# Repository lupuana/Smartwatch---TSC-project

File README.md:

# Smartwatch — TSC Project

> A custom-designed smartwatch based on the **Nordic nRF52840** SoC, featuring an e-paper display interface, haptic feedback, accelerometer-based motion sensing, LiPo battery management, and Bluetooth Low Energy connectivity. The PCB measures **46 × 35 mm** with rounded corners and is designed to fit inside a 3D-printed enclosure.

---

## Table of Contents

1. [Block Diagram](#block-diagram)
2. [Bill of Materials (BOM)](#bill-of-materials-bom)
3. [Hardware Description](#hardware-description)
4. [nRF52840 Pin Assignments](#nrf52840-pin-assignments)
5. [PCB Images](#pcb-images)
6. [Mechanical / Enclosure](#mechanical--enclosure)
7. [Design Notes](#design-notes)

---

## Block Diagram

```
                          ┌───────────────────────────────────────────────────────────────────┐
                          │                        nRF52840 (U1)                              │
                          │   ARM Cortex-M4F @ 64 MHz · 1 MB Flash · 256 KB RAM · BLE 5.0   │
                          └──┬──────────┬──────────┬──────────┬──────────┬──────────┬────────┘
                             │          │          │          │          │          │
                    SPI Bus  │   I2C Bus│  I2C Bus │  GPIO    │  SWD     │  GPIO    │  GPIO
                             │          │          │          │          │          │
               ┌─────────────▼──┐  ┌───▼────┐ ┌──▼──────┐  │   ┌──────▼──────┐  ┌▼───────┐
               │  E-Paper (EPD) │  │ BMA423 │ │DRV2605  │  │   │ TC2030-IDC  │  │ 3× SW  │
               │  24-pin FPC    │  │ Accel. │ │ Haptic  │  │   │ SWD Debug   │  │(UP/DN/ │
               │  (J1 Molex)    │  │ (IC3)  │ │ Driver  │  │   │ Connector   │  │  ENT)  │
               └────────────────┘  └────────┘ │ (IC2)   │  │   └─────────────┘  └────────┘
                                              └─────────┘  │
                                                           │
                          ┌────────────────────────────────┼──────────────────────────────────┐
                          │              Power System       │                                  │
                          │                                 │                                  │
               ┌──────────▼──┐   ┌──────────┐   ┌────────▼──────┐   ┌──────────────────┐   │
               │ USB Type-C  │   │BQ25180   │   │  MAX17048     │   │   RT6160AWSC     │   │
               │  (J4)       ├──►│ LiPo     │   │  Fuel Gauge   │   │  Buck-Boost Reg. │   │
               │ + ESD D3    │   │ Charger  │   │  (U3) I2C     │   │  (IC9) I2C       │   │
               └─────────────┘   │ (IC1)    │   └───────────────┘   └──────────────────┘   │
                                 └────┬─────┘                                                │
                                      │ VBAT                                                 │
                                 ┌────▼─────┐                                                │
                                 │  LiPo    │                                                │
                                 │ Battery  │                                                │
                                 │ (J3 pad) │                                                │
                                 └──────────┘                                                │
                                                                                             │
               ┌──────────────────────────────────────────────────────────────────┐          │
               │                    RF Front-End                                   │          │
               │  32 MHz XTAL (X1) · 32.768 kHz XTAL (X2) · ANT1 2.45 GHz       │◄─────────┘
               │  Matching network: L1 3.9 nH · L2 10 µH · L3 15 nH             │
               └──────────────────────────────────────────────────────────────────┘
```

---

## Bill of Materials (BOM)

> Procurement links point to **JLCPCB Parts** where available; datasheets linked to official manufacturer sources.

| Ref(s) | Qty | Value / Part | Description | Package | JLCPCB / Buy Link | Datasheet |
|---|---|---|---|---|---|---|
| U1 | 1 | NRF52840-QIAA | Nordic nRF52840 SoC — main MCU, BLE 5.0, ARM Cortex-M4F | AQFN-73 (aQFN50) | [JLCPCB C190794](https://jlcpcb.com/partdetail/NordicSemiconductor-NRF52840_QIAA/C190794) | [Datasheet](https://infocenter.nordicsemi.com/pdf/nRF52840_PS_v1.7.pdf) |
| IC1 | 1 | BQ25180YBGR | 1-cell LiPo charger, I²C programmable, 1 A | 8-DSBGA (1.6×1.1 mm) | [JLCPCB C2828062](https://jlcpcb.com/partdetail/TexasInstruments-BQ25180YBGR/C2828062) | [Datasheet](https://www.ti.com/lit/ds/symlink/bq25180.pdf) |
| IC2 | 1 | DRV2605YZFR | Haptic driver for ERM/LRA motors, I²C, built-in waveform library | 9-BGA (1.44×1.44 mm) | [JLCPCB C529659](https://jlcpcb.com/partdetail/TexasInstruments-DRV2605YZFR/C529659) | [Datasheet](https://www.ti.com/lit/ds/symlink/drv2605.pdf) |
| IC3 | 1 | BMA423 | Triaxial 12-bit accelerometer, step counter, I²C/SPI | LGA-12 (2×2 mm) | [JLCPCB C332973](https://jlcpcb.com/partdetail/BoschSensortec-BMA423/C332973) | [Datasheet](https://www.bosch-sensortec.com/media/boschsensortec/downloads/datasheets/bst-bma423-ds000.pdf) |
| IC9 | 1 | RT6160AWSC | Buck-boost DC-DC converter, I²C, 15-pin WL-CSP | BGA-15 (1.4×2.3 mm) | [JLCPCB C2834980](https://jlcpcb.com/partdetail/Richtek-RT6160AWSC/C2834980) | [Datasheet](https://www.richtek.com/assets/product_file/RT6160A/DS6160A-00.pdf) |
| U3 | 1 | MAX17048G+T10 | 1-cell/2-cell LiPo fuel gauge, I²C ModelGauge | TDFN-8 (2×2 mm) | [JLCPCB C368489](https://jlcpcb.com/partdetail/MaximIntegrated-MAX17048G_T10/C368489) | [Datasheet](https://www.analog.com/media/en/technical-documentation/data-sheets/MAX17048-MAX17049.pdf) |
| J1 | 1 | 503480-2400 | Molex 0.5 mm FPC/FFC 24-circuit RA SMT dual-contact connector (EPD) | — | [Mouser 538-503480-2400](https://www.mouser.com/ProductDetail/Molex/503480-2400) | [Datasheet](https://www.molex.com/en-us/products/part-detail/5034802400) |
| J2 | 1 | TC2030-IDC | Tag-Connect 6-pin SWD programming/debug header (no-drill) | TC2030IDC | [Tag-Connect](https://www.tag-connect.com/product/tc2030-idc-nl) | [Info](https://www.tag-connect.com/wp-content/uploads/bsk-pdf-manager/TC2030-IDC-NL_Datasheet_8.pdf) |
| J4 | 1 | KH-TYPE-C-16P | USB Type-C 16-pin SMT receptacle | — | [LCSC C2832](https://www.lcsc.com/product-detail/USB-Connectors_Kinghelm-KH-TYPE-C-16P_C2832.html) | [Datasheet](https://www.kinghelm.com.cn/product/kh-type-c-16p.html) |
| ANT1 | 1 | 2450AT18B100E | 2.45 GHz chip antenna for BLE | 3216 (1.4 mm H) | [JLCPCB C341461](https://jlcpcb.com/partdetail/JohansonTechnology-2450AT18B100E/C341461) | [Datasheet](https://www.johansontechnology.com/datasheets/2450AT18B100E/2450AT18B100E.pdf) |
| D3 | 1 | USBLC6-2SC6Y | USB ESD protection TVS diode array | SOT-23-6 | [JLCPCB C2687116](https://jlcpcb.com/partdetail/STMicroelectronics-USBLC6_2SC6Y/C2687116) | [Datasheet](https://www.st.com/resource/en/datasheet/usblc6-2.pdf) |
| D2, D4, D5 | 3 | MBR0530 | Schottky diode, 30 V / 500 mA | SOD-123 | [JLCPCB C424037](https://jlcpcb.com/partdetail/OnSemiconductor-MBR0530/C424037) | [Datasheet](https://www.onsemi.com/pdf/datasheet/mbr0530-d.pdf) |
| Q3 | 1 | SI1308EDL-T1-GE3 | N-channel MOSFET, 30 V / 1.5 A | SC-70 (SOT-323) | [JLCPCB C145826](https://jlcpcb.com/partdetail/VishayIntertech-Si1308EDL_T1_GE3/C145826) | [Datasheet](https://www.vishay.com/docs/63533/si1308edl.pdf) |
| DMG2305UX-7 | 1 | DMG2305UX-7 | P-channel MOSFET, 20 V / 4.2 A | SOT-23 | [JLCPCB C145702](https://jlcpcb.com/partdetail/Diodes-DMG2305UX7/C145702) | [Datasheet](https://www.diodes.com/assets/Datasheets/DMG2305UX.pdf) |
| SW_UP, SW_DN, SW_ENT | 3 | EVP-AKE31A | Panasonic SMD tactile push-button | — | [Digi-Key P123437TR-ND](https://www.digikey.com/en/products/detail/panasonic-electronic-components/EVP-AKE31A/3071225) | [Datasheet](https://industrial.panasonic.com/cdbs/www-data/pdf/ATV0000/ATV0000CE22.pdf) |
| X1 | 1 | 32 MHz crystal | RF clock for nRF52840 BLE | 2016 (2.0×1.6 mm) | [JLCPCB C9003](https://jlcpcb.com/partdetail/9003-CX2016DB32000D0GEJCC/C9003) | [Nordic recommended crystals](https://infocenter.nordicsemi.com/topic/ps_nrf52840/chapters/radio/doc/radio.html) |
| X2 | 1 | 32.768 kHz crystal | RTC/low-power clock | 3215 (3.2×1.5 mm) | [JLCPCB C32346](https://jlcpcb.com/partdetail/Hosonic-E3SB32E002400TR/C32346) | [Nordic RTC guidance](https://infocenter.nordicsemi.com/topic/ps_nrf52840/chapters/clock/doc/clock.html) |
| L1 | 1 | 3.9 nH inductor | RF matching, 0402 | 0402 | [JLCPCB C70268](https://jlcpcb.com/partdetail/70268-CL05NPC3N9BANC/C70268) | — |
| L2 | 1 | 10 µH inductor | BLE DC supply filter, 0402 | 0402 | [JLCPCB C1046](https://jlcpcb.com/partdetail/1046-CL31A226KAHNNNE/C1046) | — |
| L3 | 1 | 15 nH inductor | RF matching, 0402 | 0402 | [JLCPCB C70268](https://jlcpcb.com/partdetail/70268-CL05NPC3N9BANC/C70268) | — |
| L5 | 1 | 744043680 (68 µH) | Würth EP power inductor for buck-boost | 4828 (WE-TPC) | [JLCPCB C408386](https://jlcpcb.com/partdetail/WurthElektronik-744043680/C408386) | [Datasheet](https://www.we-online.com/en/components/products/WE-TPC#744043680) |
| L7 | 1 | FTC252012SR47MBCA | 0.47 µH power inductor for battery charger | MLP2016 (2×1.6 mm) | [JLCPCB C5832368](https://jlcpcb.com/partdetail/6763488-FTC252012SR47MBCA/C5832368) | [Datasheet](https://product.tdk.com/en/search/inductor/inductor/smd/info?part_no=FTC252012SR47MBCA) |
| C1–C43, EPD_Cx | ~50 | Various caps | Decoupling / bypass / filter (1 pF – 22 µF) | 0201, 0402 | JLCPCB standard passives | — |
| R1–R18, R_* | ~20 | Various resistors | Pull-ups, current-sense, type-select (0 Ω – 10 kΩ) | 0201 | JLCPCB standard passives | — |
| SJ1 | 1 | Solder jumper | EPD power rail selection | — | — | — |
| TP_* | 14 | Test pads | GND, 3V3, VBAT, SDA, SCL, SWDCLK, SWDIO, SWO, RESET, etc. | TP20R | — | — |

---

## Hardware Description

### 1. Microcontroller — Nordic nRF52840 (U1)

The nRF52840 is the heart of the project. It is an ARM Cortex-M4F SoC running at up to 64 MHz, with 1 MB of internal Flash, 256 KB RAM, and an integrated BLE 5.0 + 802.15.4 radio. It was chosen for its best-in-class sleep current (~2 µA in System OFF with RAM retention), its rich peripheral set (SPI, I²C, UART, USB, SWD), and its support for the Nordic SDK / Zephyr RTOS.

The chip is clocked by two external crystals: a 32 MHz crystal (X1) used as the main RF clock, and a 32.768 kHz crystal (X2) used by the RTC for low-power timekeeping. The RF matching network (L1 3.9 nH, L3 15 nH, and associated capacitors) connects the chip's antenna output to the chip antenna ANT1.

### 2. E-Paper Display Interface

The e-paper display (EPD) connects through a **Molex 503480-2400** 24-pin 0.5 mm pitch FPC right-angle connector (J1). The display is driven over **SPI** from the nRF52840. A dedicated group of capacitors (EPD_C1–EPD_C12, all 1 µF/50 V in 0402) and a filter capacitor (EPD_C5, 100 nF/50 V) provide local bypass for the EPD power rails. A solder jumper (SJ1) allows selecting the EPD supply source. The P-channel MOSFET (DMG2305UX-7) acts as a load switch to cut EPD power when the display is not being updated, minimising average current draw.

> **Note:** The display module itself is not included in this design iteration — the FPC connector and power circuitry are present and ready for integration.

### 3. Power Management

Power management is implemented with a three-chip solution:

**BQ25180YBGR (IC1) — LiPo Charger.** This Texas Instruments single-cell charger accepts 5 V from the USB Type-C port and charges a LiPo battery at up to 1 A. Charge current is configured via a current-sense resistor (R1_EP_DR, 0.47 Ω). The charger communicates with the nRF52840 over I²C for status reporting and charge parameter programming. An inductor L7 (0.47 µH) is used in the switch-mode charging path. Schottky diodes D2, D4, D5 (MBR0530) protect against reverse current conditions.

**MAX17048G+T10 (U3) — Fuel Gauge.** This Analog Devices ModelGauge IC measures the battery state-of-charge using a voltage-based algorithm, eliminating the need for a series current-sense resistor. It communicates over I²C and draws only 3 µA during normal operation, making it suitable for always-on battery monitoring.

**RT6160AWSC (IC9) — Buck-Boost Regulator.** This Richtek I²C-programmable buck-boost converter maintains a stable 3.3 V output rail (VREG) from the LiPo battery voltage, which can range from ~3.0 V (discharged) to 4.2 V (fully charged). The output voltage is dynamically adjustable via I²C, and the converter supports up to ~600 mA output current. The large 68 µH inductor L5 (Würth 744043680) is used in the power conversion path.

**USB Protection.** The USB Type-C port (J4) is protected by a USBLC6-2SC6Y (D3) ESD TVS diode array in SOT-23-6, clamping transients to a safe level before they reach the nRF52840's USB pins. The USB CC lines carry 5.1 kΩ resistors (R1_USB, R2_USB) for USB-C sink identification.

### 4. Accelerometer — BMA423 (IC3)

The Bosch BMA423 is a triaxial 12-bit accelerometer with hardware step counting, activity recognition (walk, run, still), and wrist-tilt gesture detection — all computed on-chip, so the main MCU can remain in deep sleep. It connects to the nRF52840 over **I²C**. Pull-up resistors (R5, R7 — 10 kΩ each) are placed on the SDA and SCL lines. The device draws only 14 µA in low-power mode at 25 Hz ODR.

### 5. Haptic Driver — DRV2605YZFR (IC2)

The Texas Instruments DRV2605 drives an ERM (eccentric rotating mass) or LRA (linear resonant actuator) vibration motor. It contains a library of 123 pre-programmed haptic waveforms accessible over **I²C**, allowing the firmware to trigger complex tactile patterns with a single register write. Pull-up resistors R17 and R18 (3.3 kΩ each) are provided on the I²C lines shared with the haptic driver.

### 6. Navigation Buttons

Three Panasonic EVP-AKE31A SMD tactile push-buttons are placed along the bottom edge of the PCB (SW_UP, SW_DN, SW_ENT), corresponding to UP, DOWN, and ENTER/SELECT functions. Each button connects to a GPIO pin of the nRF52840 with 10 kΩ pull-up resistors (R5, R7, R8). The nRF52840's internal sense and GPIO interrupt mechanisms enable wake-from-sleep on button press.

### 7. BLE Antenna

The 2.45 GHz chip antenna 2450AT18B100E from Johanson Technology (ANT1) is a compact 3.2×1.6 mm ceramic antenna placed at the top edge of the PCB, away from ground pours to maximise radiation efficiency. The matching network (L1, L3, and associated capacitors C3, C4) is tuned for 50 Ω impedance at 2.45 GHz as recommended by the nRF52840 reference design.

### 8. Debug / Programming Interface

A Tag-Connect TC2030-IDC footprint (J2) provides a 6-pin no-drill SWD debug interface, exposing SWDCLK, SWDIO, SWO, RESET, GND, and VCC. Dedicated test points (TP_SWDCLK, TP_SWDIO, TP_SWO, TP_RESET) are accessible on the PCB for bench probing.

### 9. Power Consumption Estimates

| Mode | Dominant Consumer | Estimated Current |
|---|---|---|
| BLE advertising (1 Hz) | nRF52840 radio | ~20 µA average |
| BLE connected (15 ms CI) | nRF52840 radio | ~5–8 mA peak, ~500 µA avg |
| EPD full refresh | EPD + nRF52840 | ~20 mA peak, ~2 s |
| Accelerometer step count only | BMA423 | ~14 µA |
| Haptic pulse (100 ms) | DRV2605 + motor | ~50–120 mA peak |
| System OFF (deep sleep) | nRF52840, fuel gauge | ~5–8 µA |

With a typical 150–300 mAh LiPo battery and BLE advertising once per second, an estimated **5–10 days** of battery life is achievable when the EPD is updated only a few times per day.

---

## nRF52840 Pin Assignments

| nRF52840 Pin | Signal Name | Connected To | Interface | Notes |
|---|---|---|---|---|
| P0.02 | AREF | ADC reference | Analog | Optional ADC reference |
| P0.04 / AIN2 | BATTERY_ADC | VBAT resistor divider | ADC | Battery voltage sense backup |
| P0.06 | UART_TX | Debug UART | UART | Optional logging |
| P0.08 | UART_RX | Debug UART | UART | Optional logging |
| P0.11 | SW_UP | SW_UP button | GPIO IN | Active-low, pull-up 10 kΩ |
| P0.12 | SW_DN | SW_DN button | GPIO IN | Active-low, pull-up 10 kΩ |
| P0.13 | SW_ENT | SW_ENT button | GPIO IN | Active-low, pull-up 10 kΩ |
| P0.14 / SDA | I2C_SDA | BMA423, DRV2605, BQ25180, MAX17048, RT6160 | I²C | 10 kΩ pull-up to 3V3 |
| P0.15 / SCL | I2C_SCL | BMA423, DRV2605, BQ25180, MAX17048, RT6160 | I²C | 10 kΩ pull-up to 3V3 |
| P0.16 | EPD_MOSI | EPD SPI data | SPI | — |
| P0.17 | EPD_SCK | EPD SPI clock | SPI | — |
| P0.18 / RESET | nRESET | TP_RESET, TC2030 | Reset | Active-low hardware reset |
| P0.19 | EPD_CS | EPD chip select | SPI / GPIO | Active-low |
| P0.20 | EPD_DC | EPD data/command select | GPIO | — |
| P0.21 | EPD_RST | EPD hardware reset | GPIO | Active-low |
| P0.22 | EPD_BUSY | EPD busy signal | GPIO IN | Input, pulled low by EPD |
| P0.23 | EPD_PWR_EN | DMG2305UX-7 gate | GPIO | Controls EPD power switch |
| P0.26 | VIB_EN | DRV2605 IN/TRIG | GPIO | Haptic trigger |
| P0.31 / AIN7 | BAT_SENSE | MAX17048 / VBAT | ADC / I²C | Fuel gauge interrupt line |
| P1.00 | SWO | TC2030-IDC pin 6 | SWD | Trace output |
| SWDIO | SWDIO | TC2030-IDC pin 2, TP_SWDIO | SWD | — |
| SWDCLK | SWDCLK | TC2030-IDC pin 4, TP_SWDCLK | SWD | — |
| GND | GND | Common ground, TP_GND | — | Multiple ground test points |
| VDD | 3V3 (from RT6160) | Decoupling caps C5–C19 etc. | Power | Per Nordic reference layout |
| VDDMAIN | 3V3 | Bulk decoupling | Power | — |
| XC1 / XC2 | 32 MHz XTAL | X1 | XTAL | Pins per nRF52840 datasheet |
| XL1 / XL2 | 32.768 kHz XTAL | X2 | XTAL | Pins per nRF52840 datasheet |
| ANT | RF output | L1 → ANT1 | RF | Via matching network |

---

## PCB Images

### 2D Layout — Top Layer

### 2D Layout — Bottom Layer

### 2D Layout — Combined (Top + Bottom)

### 3D Render — Top

### 3D Render — Bottom

### PCB Dimensions

The PCB is **46.00 mm × 35.00 mm** with a cut-out on the left side (7.00 mm wide × 13.80 mm tall) accommodating the LiPo battery connector tab and the FPC connector J1 for the e-paper display.

---

## Mechanical / Enclosure

The enclosure consists of three layers visible in the exploded view:

1. **Top bezel** — a rectangular frame (black) with a rectangular opening for the e-paper display window.
2. **PCB assembly** — the 46×35 mm PCB sits in the middle, with the USB-C port and buttons accessible through slots/holes in the case sides.
3. **Battery + bottom shell** — the LiPo battery sits below the PCB in the bottom half of the case. The bottom shell is rounded and ergonomic, designed for wrist wear.

The 3D model is provided in Fusion 360 format (`.f3z`) in the `Mechanical/` folder.

---

## Design Notes

- **No display in current iteration:** The e-paper display and its FPC cable are intentionally omitted from the current hardware build. All EPD power and SPI signals are routed and terminated at the Molex FPC connector, ready for the next revision.
- **I²C bus sharing:** BMA423, DRV2605, BQ25180, MAX17048, and RT6160 all share a single I²C bus. Each device has a unique 7-bit address, and the bus pull-ups (10 kΩ) are placed once on the PCB. Bus speed is 400 kHz (Fast Mode).
- **EPD power isolation:** The DMG2305UX-7 P-MOSFET switches the EPD supply rail off when not refreshing. This prevents the display from drawing quiescent current during sleep, which can be 50–200 µA on typical e-paper modules.
- **USB-C:** Only USB 2.0 full-speed is implemented (nRF52840 native USB), sufficient for DFU firmware updates and serial logging. The CC resistors (5.1 kΩ) configure the device as a standard 5V/500 mA sink.
- **Gerber files** for manufacturing are located in `Manufacturing/gerbers.zip`.
- **License:** MIT — see `LICENSE` for details.

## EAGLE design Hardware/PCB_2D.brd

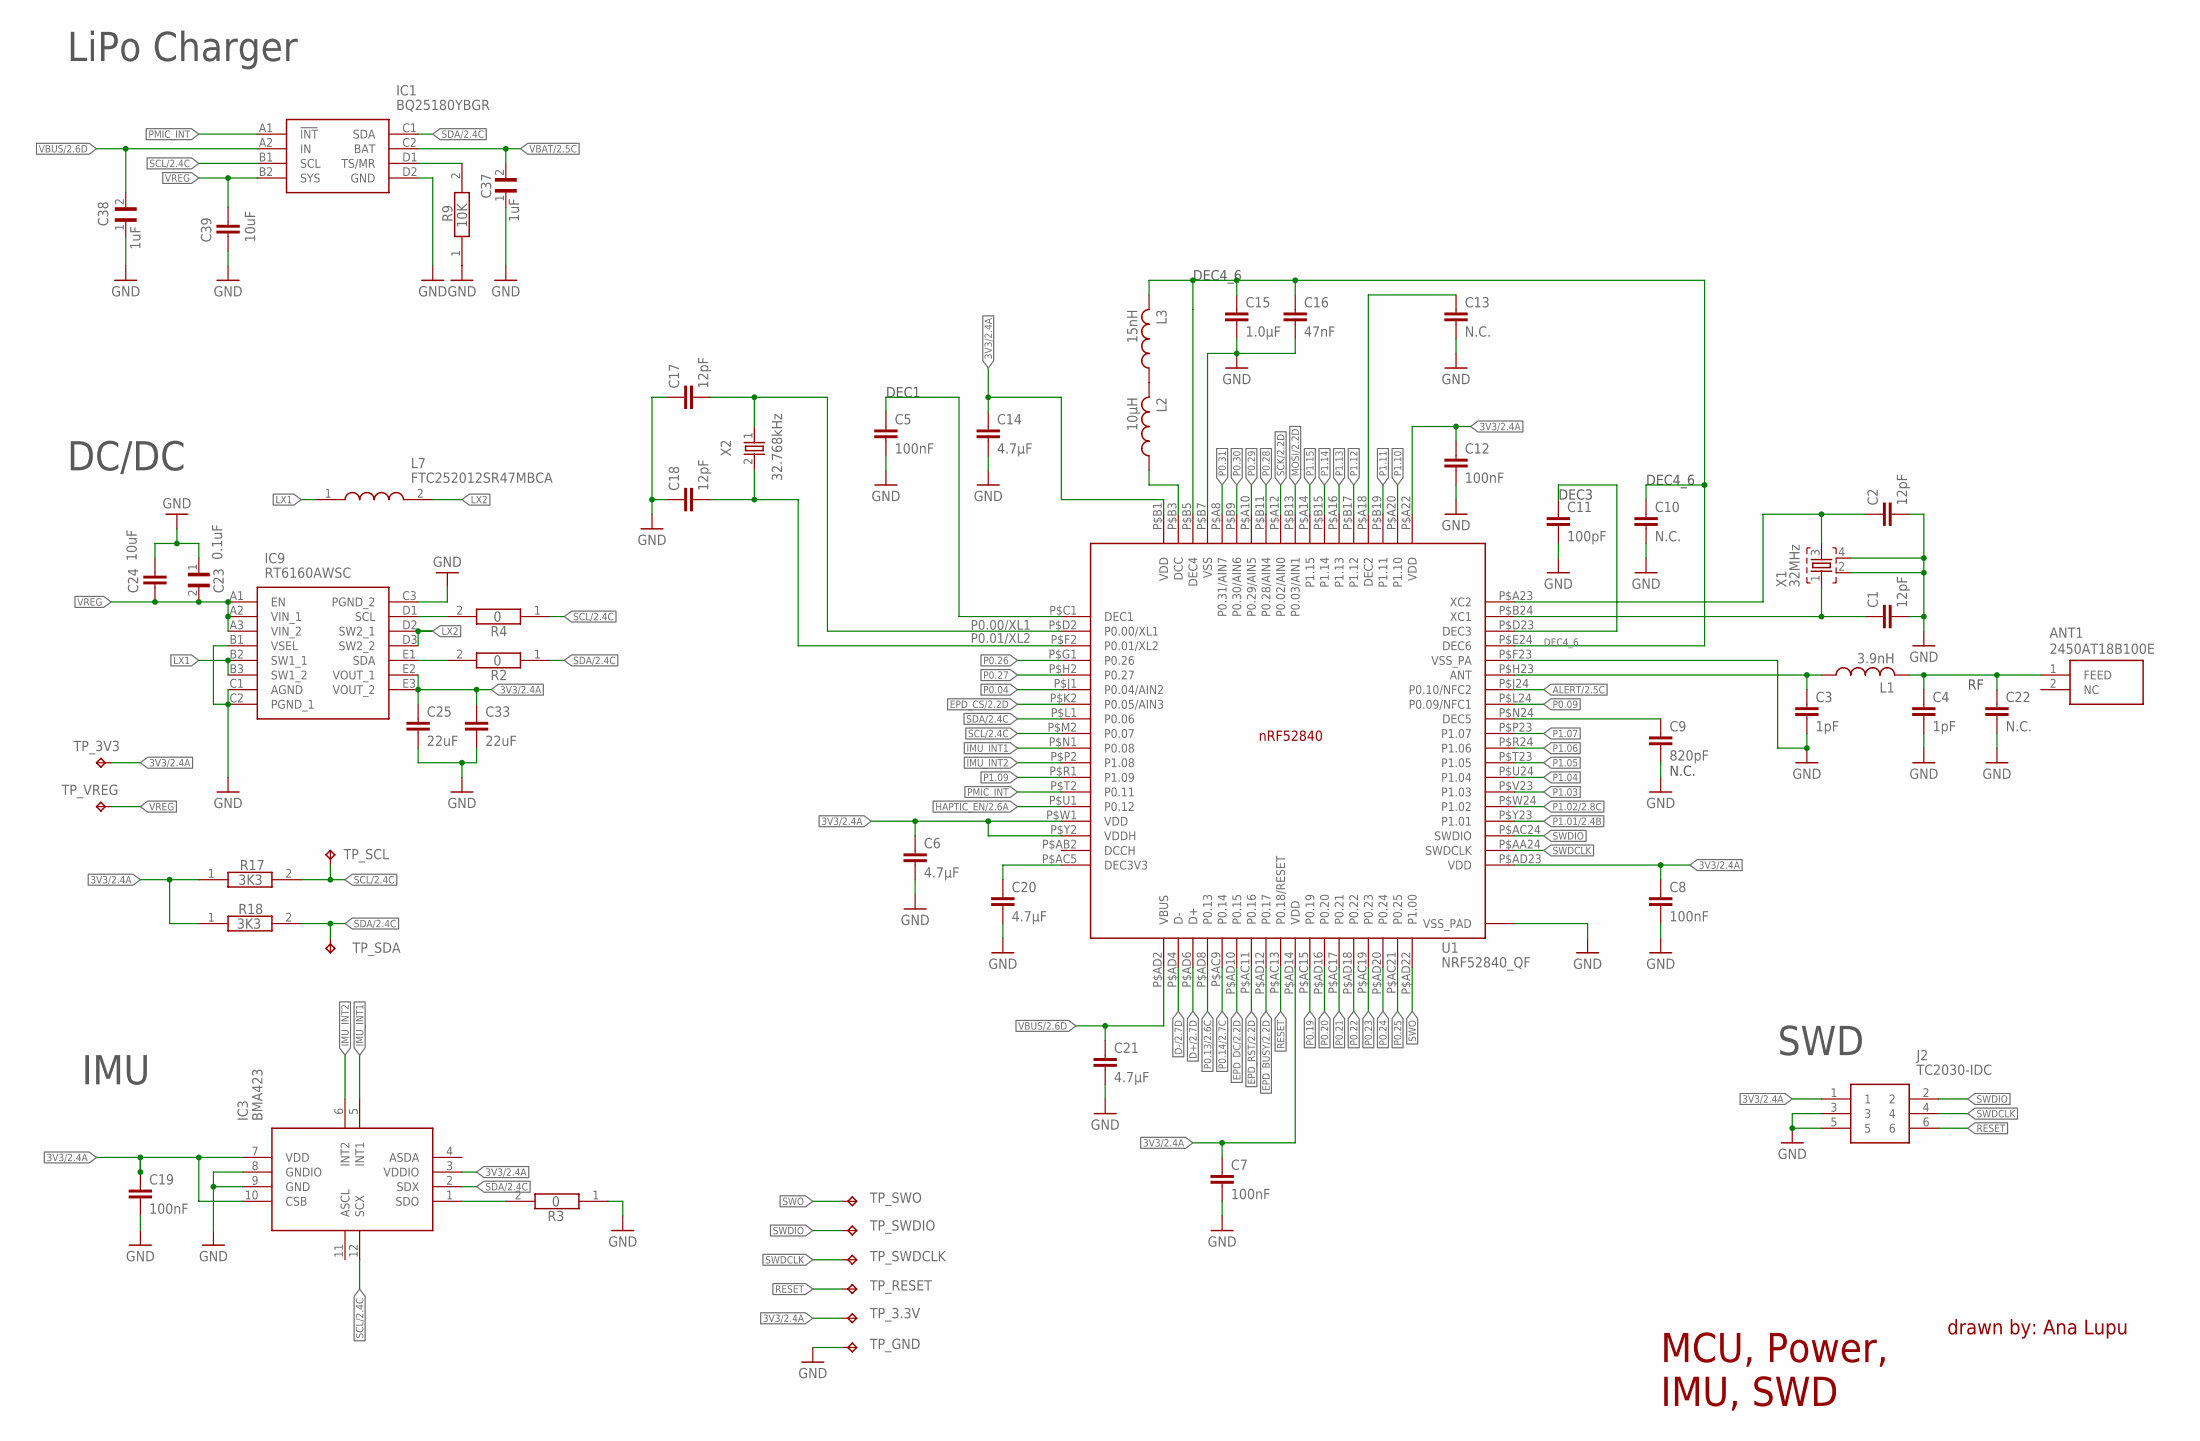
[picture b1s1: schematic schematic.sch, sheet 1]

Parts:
ANT1: 2450AT18B100E; 2450AT18B100E_ANTC3216X140N
C1, C2, C17, C18: 12pF; NORDIC_NRF_3_RESC0201_L
C3, C4: 1pF; NORDIC_NRF_3_RESC0201_L
C5, C7, C8, C12, C19: 100nF; NORDIC_NRF_3_RESC0201_L
C6, C14, C20, C21: 4.7µF; PERFECT_0402_0402
C9: 820pF; NORDIC_NRF_3_RESC0201_L
C10, C13, C22: N.C.; NORDIC_NRF_3_RESC0201_L
C11: 100pF; NORDIC_NRF_3_RESC0201_L
C15: 1.0µF; PERFECT_0402_0402
C16: 47nF; NORDIC_NRF_3_RESC0201_L
C23: 0.1uF; GRM011R60J152KE01L_2_CAPC0201X13N
C24, C39: 10uF; PERFECT_0402_0402
C25, C33: 22uF; PERFECT_0402_0402
C37, C38: 1uF; GRM011R60J152KE01L_2_CAPC0201X13N
IC1: BQ25180YBGR; BQ25180YBGR_BGA8C40P2X4_100X155X50
IC3: BMA423; BMA423_BMA423
IC9: RT6160AWSC; RT6160AWSC_BGA15C40P3X5_140X230X60
J2: TC2030-IDC; TC2030-IDC_TC2030IDC
L1: 3.9nH; NORDIC_NRF_2_RESC0402_M
L2: 10μH; NORDIC_NRF_2_RESC0402_M
L3: 15nH; NORDIC_NRF_2_RESC0402_M
L7: FTC252012SR47MBCA; MLP2016SR47MT0S1_INDC2016X100N
R2, R3, R4: 0; CPF0201D7K68C1_0201
R9: 10K; CPF0201D7K68C1_0201
R17, R18: 3K3; CPF0201D7K68C1_0201
TP_3.3V, TP_3V3: HECTOR_WATCH_1_TPTP20R; HECTOR_WATCH_1_TP20R
TP_GND: HECTOR_WATCH_1_TPTP20R; HECTOR_WATCH_1_TP20R
TP_RESET: HECTOR_WATCH_1_TPTP20R; HECTOR_WATCH_1_TP20R
TP_SCL: HECTOR_WATCH_1_TPTP20R; HECTOR_WATCH_1_TP20R
TP_SDA: HECTOR_WATCH_1_TPTP20R; HECTOR_WATCH_1_TP20R
TP_SWDCLK: HECTOR_WATCH_1_TPTP20R; HECTOR_WATCH_1_TP20R
TP_SWDIO: HECTOR_WATCH_1_TPTP20R; HECTOR_WATCH_1_TP20R
TP_SWO: HECTOR_WATCH_1_TPTP20R; HECTOR_WATCH_1_TP20R
TP_VREG: HECTOR_WATCH_1_TPTP20R; HECTOR_WATCH_1_TP20R
U1: NRF52840_QF; NORDIC_NRF_4_AQFN50P700X700X85_HS-74N
X1: 32MHz; NORDIC_NRF_BT-XTAL_2016_N
X2: 32.768kHz; NORDIC_NRF_1_XTAL_3215_N

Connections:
3V3/2.4A: C6.1, C7.1, C8.1, C12.1, C14.1, C19.1, C25.1, C33.1, IC3.3 (VDDIO), IC3.7 (VDD), IC3.10 (CSB), IC9.E2 (VOUT_1), IC9.E3 (VOUT_2), J2.1, R17.1, R18.1, TP_3.3V.TP, TP_3V3.TP, U1.P$A22 (VDD), U1.P$AD14 (VDD), U1.P$AD23 (VDD), U1.P$B1 (VDD), U1.P$W1 (VDD), U1.P$Y2 (VDDH)
ALERT/2.5C: U1.P$J24 (P0.10/NFC2)
D+/2.7D: U1.P$AD6 (D+)
D-/2.7D: U1.P$AD4 (D-)
DEC4_6: C10.1, C15.1, C16.1, L3.2, U1.P$B5 (DEC4), U1.P$E24 (DEC6)
EPD_BUSY/2.2D: U1.P$AD12 (P0.17)
EPD_CS/2.2D: U1.P$K2 (P0.05/AIN3)
EPD_DC/2.2D: U1.P$AD10 (P0.15)
EPD_RST/2.2D: U1.P$AC11 (P0.16)
GND: C1.2, C2.2, C3.2, C4.2, C5.2, C6.2, C7.2, C8.2, C9.2, C10.2, C11.2, C12.2, C13.2, C14.2, C15.2, C16.2, C17.1, C18.1, C19.2, C20.2, C21.2, C22.2, C23.1, C24.1, C25.2, C33.2, C37.1, C38.1, C39.2, IC1.D2 (GND), IC3.8 (GNDIO), IC3.9 (GND), IC9.B1 (VSEL), IC9.C1 (AGND), IC9.C2 (PGND_1), IC9.C3 (PGND_2), J2.3, J2.5, R3.1, R9.1, TP_GND.TP, U1.P$74 (VSS_PAD), U1.P$75 (VSS_PAD), U1.P$76 (VSS_PAD), U1.P$77 (VSS_PAD), U1.P$78 (VSS_PAD), U1.P$79 (VSS_PAD), U1.P$80 (VSS_PAD), U1.P$81 (VSS_PAD), U1.P$82 (VSS_PAD), U1.P$83 (VSS_PAD), U1.P$84 (VSS_PAD), U1.P$85 (VSS_PAD), U1.P$86 (VSS_PAD), U1.P$87 (VSS_PAD), U1.P$88 (VSS_PAD), U1.P$89 (VSS_PAD), U1.P$90 (VSS_PAD), U1.P$B7 (VSS), U1.P$F23 (VSS_PA), X1.2, X1.4; also elsewhere on the board
HAPTIC_EN/2.6A: U1.P$U1 (P0.12)
IMU_INT1: IC3.5 (INT1), U1.P$N1 (P0.08)
IMU_INT2: IC3.6 (INT2), U1.P$P2 (P1.08)
LX1: IC9.B2 (SW1_1), IC9.B3 (SW1_2), L7.1
LX2: IC9.D2 (SW2_1), IC9.D3 (SW2_2), L7.2
MOSI/2.2D: U1.P$B13 (P0.03/AIN1)
unnamed: C5.1, U1.P$C1 (DEC1)
unnamed: IC1.D1 (TS/MR), R9.2
unnamed: C20.1, U1.P$AC5 (DEC3V3)
unnamed: L2.1, U1.P$B3 (DCC)
unnamed: C1.1, U1.P$B24 (XC1), X1.1
unnamed: IC9.D1 (SCL), R4.2
unnamed: C13.1, U1.P$A18 (DEC2)
unnamed: IC9.E1 (SDA), R2.2
unnamed: L2.2, L3.1
unnamed: IC3.1 (SDO), R3.2
unnamed: C9.1, U1.P$N24 (DEC5)
unnamed: ANT1.1 (FEED), C4.1, C22.1, L1.2
unnamed: C3.1, L1.1, U1.P$H23 (ANT)
unnamed: C2.1, U1.P$A23 (XC2), X1.3
unnamed: C11.1, U1.P$D23 (DEC3)
P0.00/XL1: C17.2, U1.P$D2 (P0.00/XL1), X2.1
P0.01/XL2: C18.2, U1.P$F2 (P0.01/XL2), X2.2
P0.04: U1.P$J1 (P0.04/AIN2)
P0.09: U1.P$L24 (P0.09/NFC1)
P0.13/2.6C: U1.P$AD8 (P0.13)
P0.14/2.7C: U1.P$AC9 (P0.14)
P0.19: U1.P$AC15 (P0.19)
P0.20: U1.P$AD16 (P0.20)
P0.21: U1.P$AC17 (P0.21)
P0.22: U1.P$AD18 (P0.22)
P0.23: U1.P$AC19 (P0.23)
P0.24: U1.P$AD20 (P0.24)
P0.25: U1.P$AC21 (P0.25)
P0.26: U1.P$G1 (P0.26)
P0.27: U1.P$H2 (P0.27)
P0.28: U1.P$B11 (P0.28/AIN4)
P0.29: U1.P$A10 (P0.29/AIN5)
P0.30: U1.P$B9 (P0.30/AIN6)
P0.31: U1.P$A8 (P0.31/AIN7)
P1.01/2.4B: U1.P$Y23 (P1.01)
P1.02/2.8C: U1.P$W24 (P1.02)
P1.03: U1.P$V23 (P1.03)
P1.04: U1.P$U24 (P1.04)
P1.05: U1.P$T23 (P1.05)
P1.06: U1.P$R24 (P1.06)
P1.07: U1.P$P23 (P1.07)
P1.09: U1.P$R1 (P1.09)
P1.10: U1.P$A20 (P1.10)
P1.11: U1.P$B19 (P1.11)
P1.12: U1.P$B17 (P1.12)
P1.13: U1.P$A16 (P1.13)
P1.14: U1.P$B15 (P1.14)
P1.15: U1.P$A14 (P1.15)
PMIC_INT: IC1.A1 (!INT), U1.P$T2 (P0.11)
RESET: J2.6, TP_RESET.TP, U1.P$AC13 (P0.18/RESET)
SCK/2.2D: U1.P$A12 (P0.02/AIN0)
SCL/2.4C: IC1.B1 (SCL), IC3.12 (SCX), R4.1, R17.2, TP_SCL.TP, U1.P$M2 (P0.07)
SDA/2.4C: IC1.C1 (SDA), IC3.2 (SDX), R2.1, R18.2, TP_SDA.TP, U1.P$L1 (P0.06)
SWDCLK: J2.4, TP_SWDCLK.TP, U1.P$AA24 (SWDCLK)
SWDIO: J2.2, TP_SWDIO.TP, U1.P$AC24 (SWDIO)
SWO: TP_SWO.TP, U1.P$AD22 (P1.00)
VBAT/2.5C: C37.2, IC1.C2 (BAT)
VBUS/2.6D: C21.1, C38.2, IC1.A2 (IN), U1.P$AD2 (VBUS)
VREG: C23.2, C24.2, C39.1, IC1.B2 (SYS), IC9.A1 (EN), IC9.A2 (VIN_1), IC9.A3 (VIN_2), TP_VREG.TP

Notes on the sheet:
LiPo Charger
DC/DC
IMU
SWD
MCU, Power, IMU, SWD
drawn by: Ana Lupu
N.C.
DEC1
DEC3
DEC4_6

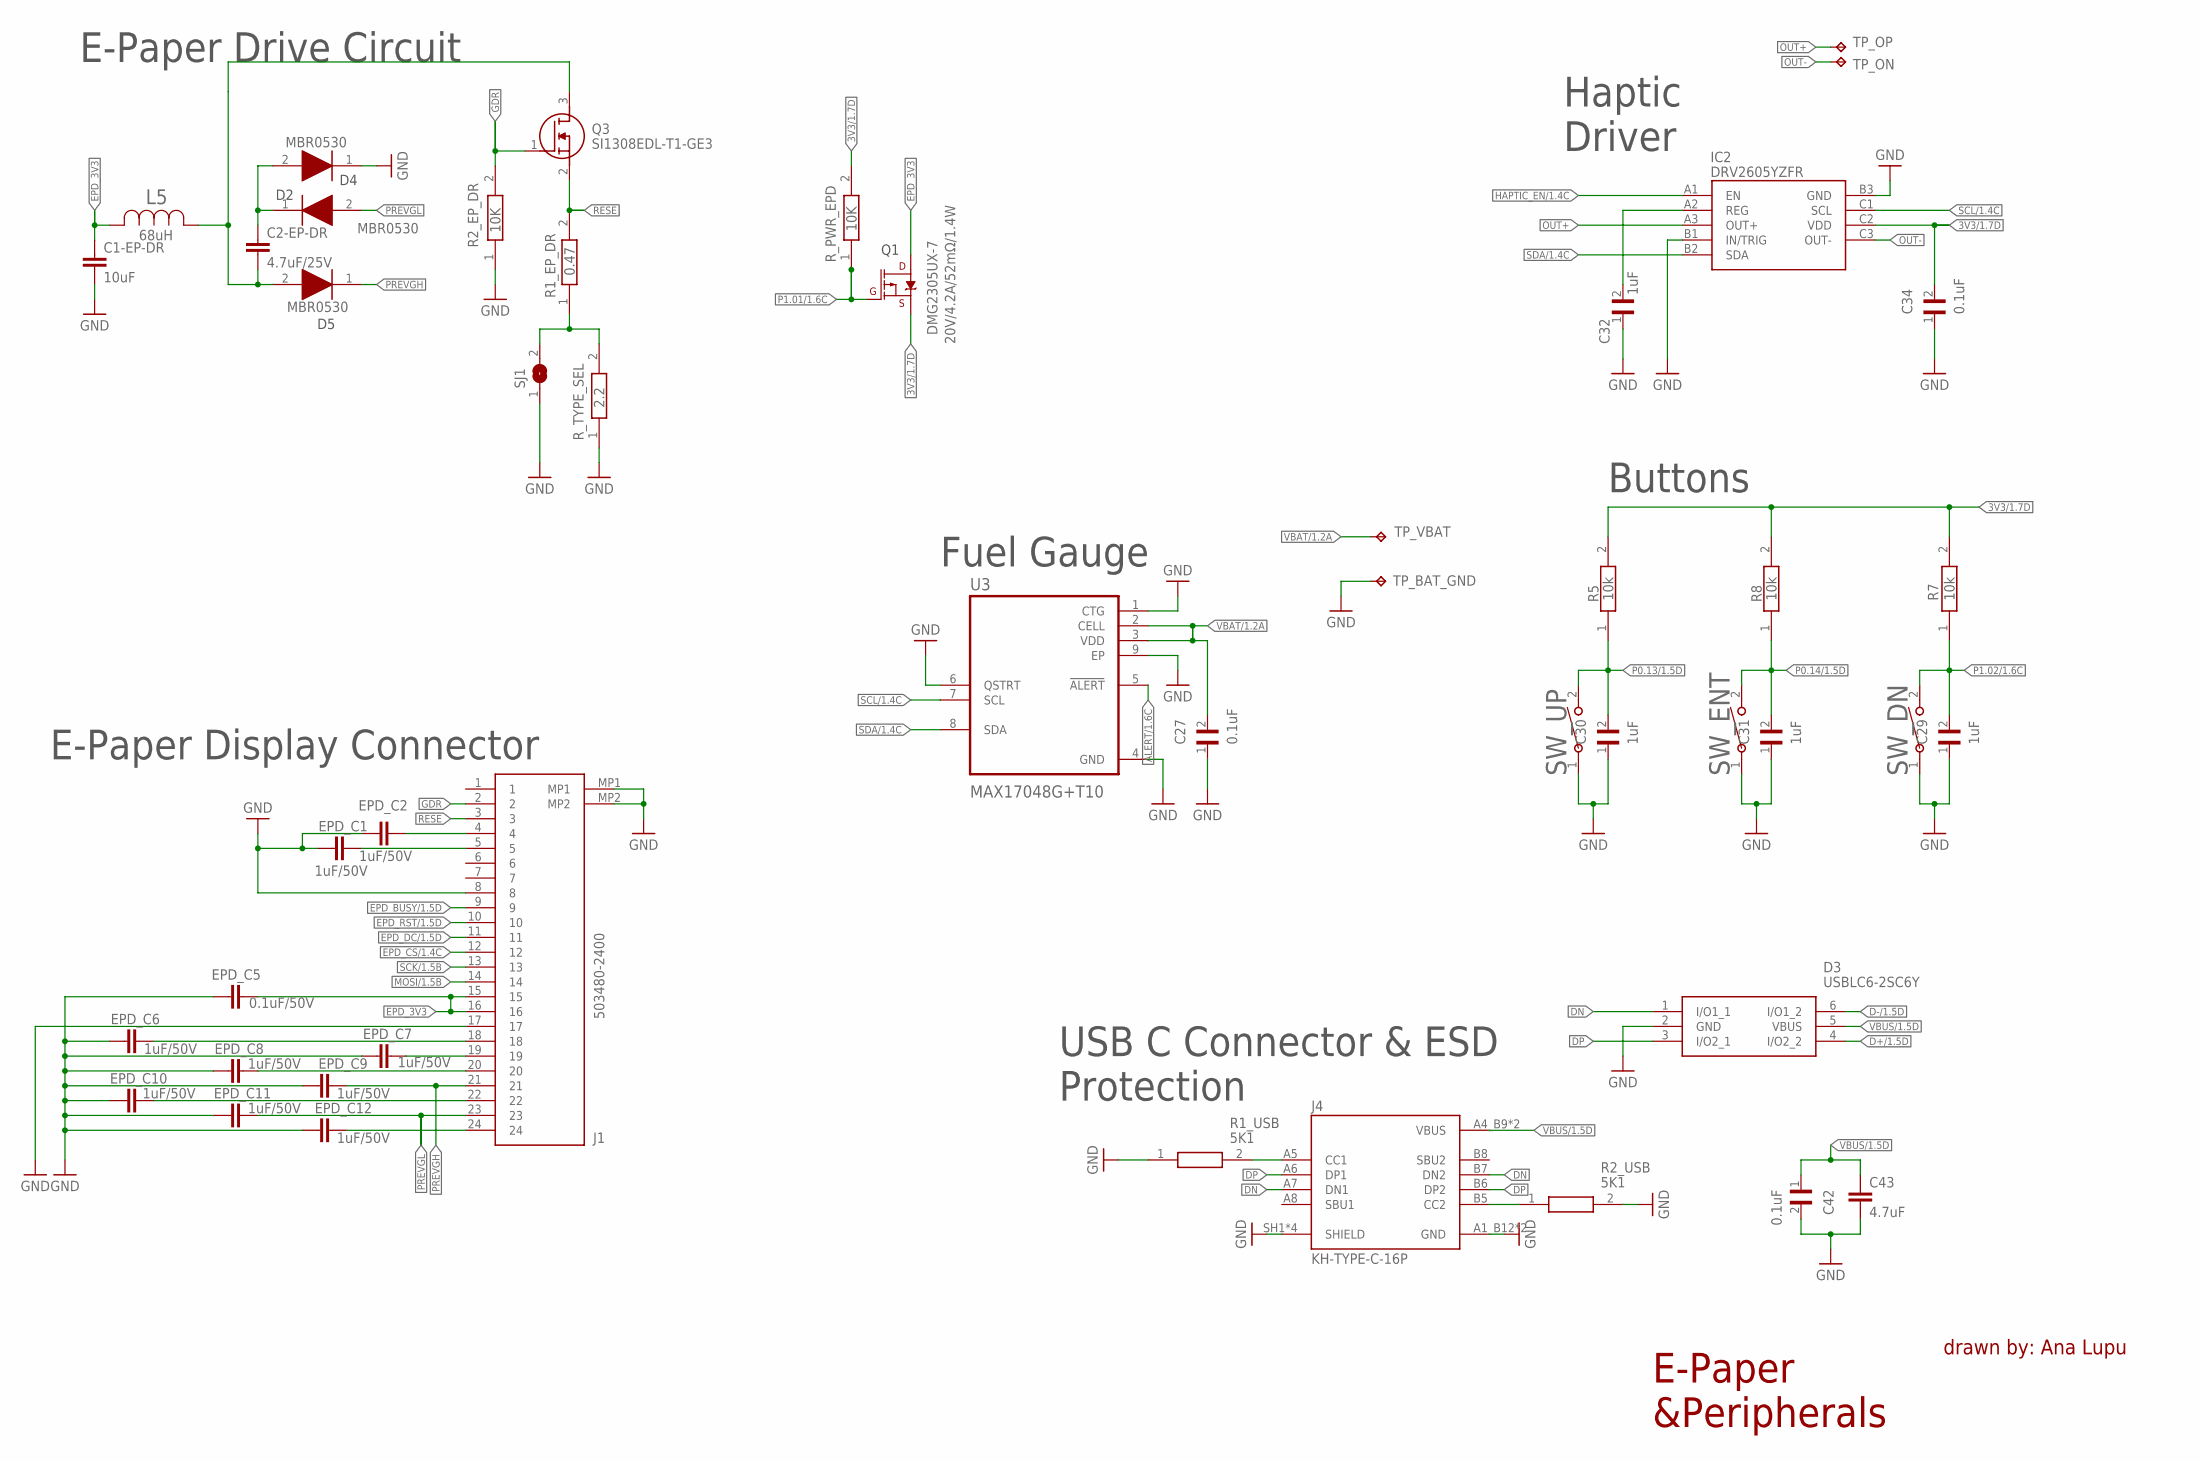
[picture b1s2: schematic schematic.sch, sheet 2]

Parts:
C1-EP-DR: 10uF; PERFECT_0402_0402
C2-EP-DR: 4.7uF/25V; PERFECT_0402_0402
C27, C34, C42: 0.1uF; GRM011R60J152KE01L_2_CAPC0201X13N
C29, C30, C31, C32: 1uF; GRM011R60J152KE01L_2_CAPC0201X13N
C43: 4.7uF; PERFECT_0402_0402
D2, D4, D5: MBR0530; ESP32_C6_LIBRARY_5_SOD3716X135N
D3: USBLC6-2SC6Y; ESP32_C6_LIBRARY_3_SOT95P280X145-6N
DMG2305UX-7: 20V/4.2A/52mΩ/1.4W; ESP32_C6_LIBRARY_4_ESP32_C6_LIBRARY_4_ESP32_C6_LIBRARY_4_ES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
EPD_C1, EPD_C2, EPD_C6, EPD_C7, EPD_C8, EPD_C9, EPD_C10, EPD_C11, EPD_C12: 1uF/50V; PERFECT_0402_0402
EPD_C5: 0.1uF/50V; NORDIC_NRF_3_RESC0201_L
IC2: DRV2605YZFR; DRV2605YZFR_BGA9C50P3X3_144X144X62
J1: 503480-2400; 503480-2400_5034802400
J4: KH-TYPE-C-16P; KH-TYPE-C-16P_KINGHELM_KH-TYPE-C-16P
L5: 68uH; ESP32_C6_LIBRARY_2_IND_4828-WE-TPC_WRE
Q3: SI1308EDL-T1-GE3; ESP32_C6_LIBRARY_6_SOT65P210X110-3N
R1_EP_DR: 0.47; ERA-1AEB3401C_0201
R1_USB, R2_USB: 5K1; ERA-1AEB3401C_0201
R2_EP_DR: 10K; ERA-1AEB3401C_0201
R5, R7, R8: 10k; ERA-1AEB3401C_0201
R_PWR_EPD: 10K; ERA-1AEB3401C_0201
R_TYPE_SEL: 2.2; ERA-1AEB3401C_0201
SJ1: ESP32_C6_LIBRARY_7_JUMPER_SJ
SW_DN: 2025-10-22_07-23-44_LIBRARY_EVP-AKE31ASW_EVP-AKE3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; 2025-10-22_07-23-44_LIBRARY_SW_EVP-AKE31A_PAN
SW_ENT: 2025-10-22_07-23-44_LIBRARY_EVP-AKE31ASW_EVP-AKE3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; 2025-10-22_07-23-44_LIBRARY_SW_EVP-AKE31A_PAN
SW_UP: 2025-10-22_07-23-44_LIBRARY_EVP-AKE31ASW_EVP-AKE3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; 2025-10-22_07-23-44_LIBRARY_SW_EVP-AKE31A_PAN
TP_BAT_GND: HECTOR_WATCH_1_TPTP20R; HECTOR_WATCH_1_TP20R
TP_ON: HECTOR_WATCH_1_TPTP20R; HECTOR_WATCH_1_TP20R
TP_OP: HECTOR_WATCH_1_TPTP20R; HECTOR_WATCH_1_TP20R
TP_VBAT: HECTOR_WATCH_1_TPTP20R; HECTOR_WATCH_1_TP20R
U3: MAX17048G+T10; ESP32_C6_LIBRARY_SON50P200X200X80-9N

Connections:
3V3/1.7D: C34.2, DMG2305UX-7.2 (S), IC2.C2 (VDD), R5.2, R7.2, R8.2, R_PWR_EPD.2
ALERT/1.6C: U3.5 (!ALERT)
D+/1.5D: D3.4 (I/O2_2)
D-/1.5D: D3.6 (I/O1_2)
DN: D3.1 (I/O1_1), J4.A7 (DN1), J4.B7 (DN2)
DP: D3.3 (I/O2_1), J4.A6 (DP1), J4.B6 (DP2)
EPD_3V3: C1-EP-DR.1, DMG2305UX-7.3 (D), EPD_C5.2, J1.15, J1.16, L5.2
EPD_BUSY/1.5D: J1.9
EPD_CS/1.4C: J1.12
EPD_DC/1.5D: J1.11
EPD_RST/1.5D: J1.10
GDR: J1.2, Q3.1 (G), R2_EP_DR.2
GND: C1-EP-DR.2, C27.1, C29.1, C30.1, C31.1, C32.1, C34.1, C42.2, C43.2, D3.2 (GND), D4.1 (K), EPD_C1.1, EPD_C2.1, EPD_C5.1, EPD_C6.1, EPD_C7.1, EPD_C8.1, EPD_C9.1, EPD_C10.1, EPD_C11.1, EPD_C12.1, IC2.B1 (IN/TRIG), IC2.B3 (GND), J1.8, J1.17, J1.MP1, J1.MP2, J4.A1_B12 (GND), J4.A12_B1 (GND), J4.SH1 (SHIELD), J4.SH2 (SHIELD), J4.SH3 (SHIELD), J4.SH4 (SHIELD), R1_USB.1, R2_EP_DR.1, R2_USB.2, R_TYPE_SEL.1, SJ1.1, SW_DN.1, SW_ENT.1, SW_UP.1, TP_BAT_GND.TP, U3.1 (CTG), U3.4 (GND), U3.6 (QSTRT), U3.9 (EP); also elsewhere on the board
HAPTIC_EN/1.4C: IC2.A1 (EN)
MOSI/1.5B: J1.14
unnamed: C2-EP-DR.2, D5.2 (A), L5.1, Q3.3 (D)
unnamed: C2-EP-DR.1, D2.1 (K), D4.2 (A)
unnamed: EPD_C2.2, J1.4
unnamed: R1_EP_DR.1, R_TYPE_SEL.2, SJ1.2
unnamed: EPD_C1.2, J1.5
unnamed: EPD_C6.2, J1.18
unnamed: EPD_C7.2, J1.19
unnamed: EPD_C8.2, J1.20
unnamed: J4.A5 (CC1), R1_USB.2
unnamed: EPD_C10.2, J1.22
unnamed: C32.2, IC2.A2 (REG)
unnamed: EPD_C12.2, J1.24
unnamed: J4.B5 (CC2), R2_USB.1
OUT+: IC2.A3 (OUT+), TP_OP.TP
OUT-: IC2.C3 (OUT-), TP_ON.TP
P0.13/1.5D: C30.2, R5.1, SW_UP.2
P0.14/1.5D: C31.2, R8.1, SW_ENT.2
P1.01/1.6C: DMG2305UX-7.1 (G), R_PWR_EPD.1
P1.02/1.6C: C29.2, R7.1, SW_DN.2
PREVGH: D5.1 (K), EPD_C9.2, J1.21
PREVGL: D2.2 (A), EPD_C11.2, J1.23
RESE: J1.3, Q3.2 (S), R1_EP_DR.2
SCK/1.5B: J1.13
SCL/1.4C: IC2.C1 (SCL), U3.7 (SCL)
SDA/1.4C: IC2.B2 (SDA), U3.8 (SDA)
VBAT/1.2A: C27.2, TP_VBAT.TP, U3.2 (CELL), U3.3 (VDD)
VBUS/1.5D: C42.1, C43.1, D3.5 (VBUS), J4.A4_B9 (VBUS), J4.A9_B4 (VBUS)

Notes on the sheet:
E-Paper Drive Circuit
Haptic Driver
E-Paper Display Connector
Fuel Gauge
Buttons
USB C Connector & ESD Protection
E-Paper &Peripherals
drawn by: Ana Lupu

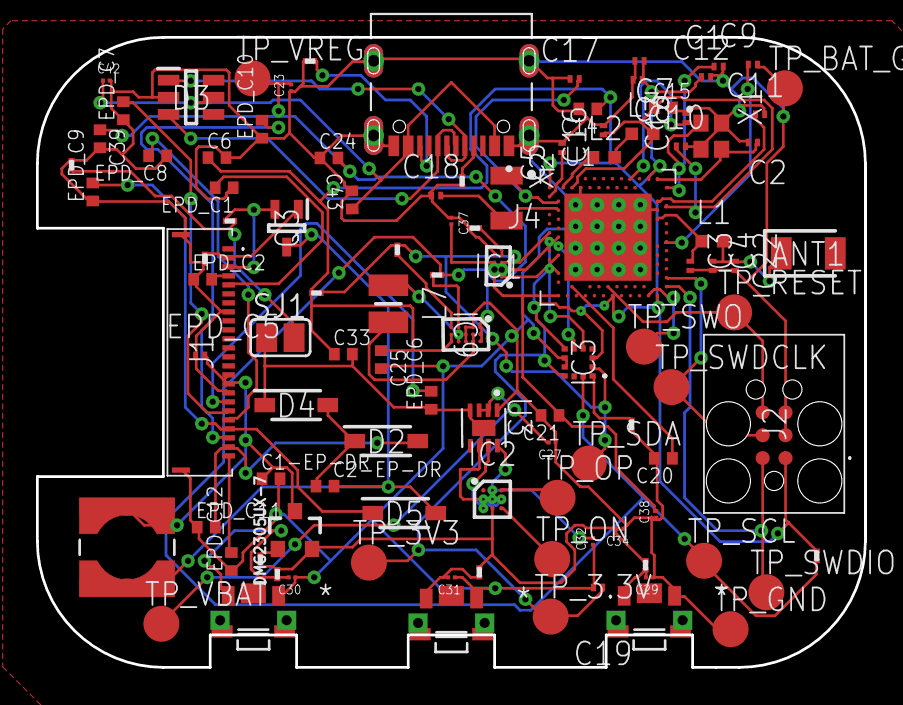
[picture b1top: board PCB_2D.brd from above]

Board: 2 copper layers, 46.0 x 35.0 mm, 105 parts (0 on the bottom side), 65 nets.

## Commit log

2026-04-10 Schematic and parts of PCB
2026-04-10 All folders
2026-04-22 done
2026-04-22 Revise README with project details and hardware overview
    Updated project title, added detailed project description, and expanded sections on hardware components, power management, and PCB layout.
2026-04-22 Update image path for exploded view in README

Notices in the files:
parts and their libraries:
COPYRIGHT: Copyright (C) 2024 Ultra Librarian. All rights reserved.
COPYRIGHT: Copyright (C) 2025 Ultra Librarian. All rights reserved.
